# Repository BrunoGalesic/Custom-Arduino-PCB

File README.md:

Custom Arduino UNO-Style Board

This project is a custom-designed Arduino UNO-style board, created with KiCad 8.0, focusing on improved RF characteristics and robust performance. It features a 4-layer PCB design with enhanced power and ground integrity, additional user controls, and thoughtful RF/EMI protections.

 Features:
 
 4-layer PCB with wider power and ground traces for reduced resistance and improved signal integrity.
 
Increased via count on tracks to enhance current capacity and minimize impedance.

Polyfuse for overcurrent protection—resistance increases with temperature rise to protect circuits.

Varistor for surge voltage protection—acts as an insulator under normal conditions and conducts to ground when voltage spikes occur.

Ferrite bead filters (BLM21) to block high-frequency noise while passing low-frequency signals.

USB port shield to mitigate EMI, acting like a Faraday cage connected to ground.

ATmega16U2-MU microcontroller for USB-to-serial conversion, enabling USB communication.

16 MHz external crystal oscillator connected via capacitors for stable clock signals.

4 pushbutton switches and a 7-segment display connected via an I2C port expander for expanded user interaction.

 Design Considerations:
 
 Emphasis on RF performance and signal integrity with multi-layer routing and shielding.
 
Thoughtful placement of components to reduce noise and EMI interference.

Added hardware elements such as TVS diodes for ESD protection on sensitive lines (like RESET).

Designed with educational intent—to explore PCB design, RF characteristics, and protection mechanisms.

 Learning Outcomes:

 The polyfuse: how it increases resistance with temperature due to excessive current.
 
The varistor: how it remains non-conductive at normal voltages and conducts during surges to ground.

The ferrite beads (BLM21): low impedance at low frequencies, high impedance at high frequencies, acting as filters.

USB shielding: how the shield connects to ground and functions like a Faraday cage to prevent EMI.

ATmega16U2-MU: an 8-bit microcontroller used for USB-to-serial conversion.

Crystal oscillators: using piezoelectric effect for stable frequency generation, needing capacitors to ground.

RF oscillators (LC and RC): in radio circuits and microcontrollers.

ICSP (In-Circuit Serial Programming) for direct microcontroller programming.

TXLED and RXLED for visual indication of data transmission and reception.

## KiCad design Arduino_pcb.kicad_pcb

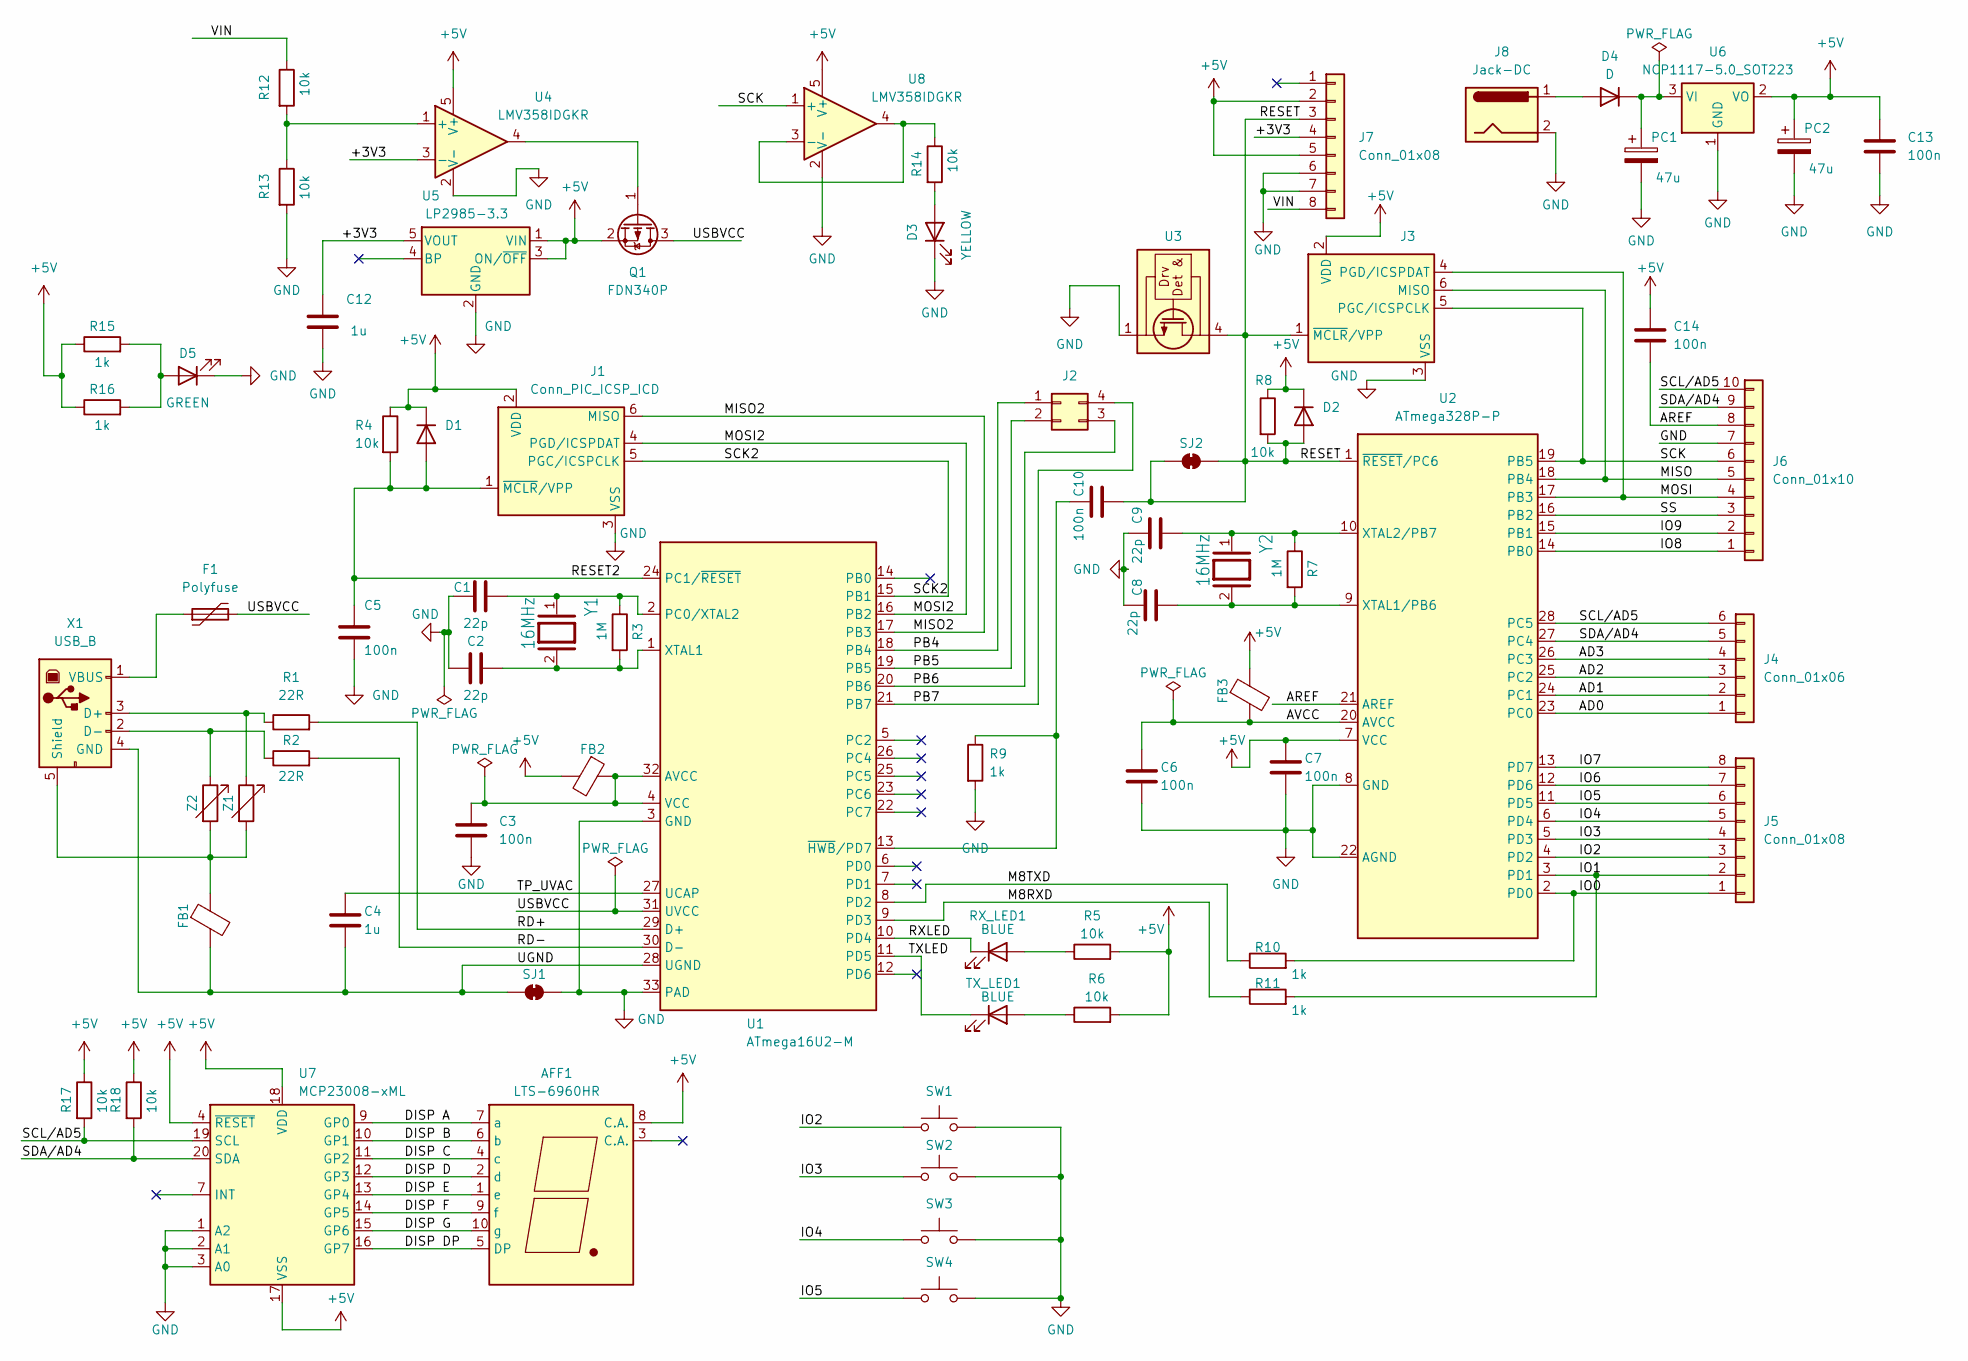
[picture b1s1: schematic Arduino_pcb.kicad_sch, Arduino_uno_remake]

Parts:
AFF1: LTS-6960HR; 7SegmentLED_LTS6760_LTS6780
C1, C2, C8, C9: 22p; C_0402_1005Metric
C3, C5: 100n; C_0603_1608Metric
C4: 1u; C_0603_1608Metric
C6, C7, C10, C13, C14: 100n; C_0201_0603Metric
C12: 1u; C_0201_0603Metric
D1, D2, D4: D; D_0603_1608Metric
D3: YELLOW; LED_0603_1608Metric
D5: GREEN; LED_0603_1608Metric
F1: Polyfuse; Fuse_0603_1608Metric
FB1, FB2, FB3: FerriteBead; L_0805_2012Metric
J1, J3: Conn_PIC_ICSP_ICD; ono
J2: Conn_02x02_Counter_Clockwise; PinHeader_2x02_P2.00mm_Vertical
J4: Conn_01x06; PinHeader_1x06_P1.00mm_Vertical
J5, J7: Conn_01x08; PinHeader_1x08_P1.00mm_Vertical
J6: Conn_01x10; PinHeader_1x10_P1.00mm_Vertical
J8: Jack-DC; BarrelJack_Horizontal
PC1, PC2: 47u; CP_Elec_6.3x5.4
Q1: FDN340P; SOT-23
R1, R2: 22R; R_0603_1608Metric
R3, R7: 1M; R_0603_1608Metric
R4, R5, R6, R8, R12, R13, R14, R17, R18: 10k; R_0603_1608Metric
R9, R10, R11, R15, R16: 1k; R_0603_1608Metric
RX_LED1: BLUE; LED_0603_1608Metric
SJ1, SJ2: SolderJumper_2_Bridged; SolderJumper-2_P1.3mm_Bridged2Bar_Pad1.0x1.5mm
SW1, SW2, SW3, SW4: SW_Push; SW_DIP_SPSTx01_Slide_6.7x4.1mm_W6.73mm_P2.54mm_LowProfile_J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
TX_LED1: BLUE; LED_0603_1608Metric
U1: ATmega16U2-M; QFN-32-1EP_5x5mm_P0.5mm_EP3.1x3.1mm
U2: ATmega328P-P; DIP-28_W7.62mm
U3: TVS3300DRV; WSON-6-1EP_2x2mm_P0.65mm_EP1x1.6mm
U4, U8: LMV358IDGKR; SOP65P490X110-8N
U5: LP2985-3.3; SOT-23-5
U6: NCP1117-5.0_SOT223; SOT-223-3_TabPin2
U7: MCP23008-xML; QFN-20-1EP_4x4mm_P0.5mm_EP2.7x2.7mm
X1: USB_B; USB_B_OST_USB-B1HSxx_Horizontal
Y1, Y2: 16MHz; Crystal_SMD_0603-2Pin_6.0x3.5mm
Z1, Z2: R_Variable; VARC1608X56N

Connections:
+5V: AFF1.8 (C.A.), C7.1, C13.1, C14.1, D1.1 (K), D2.1 (K), FB2.2, FB3.1, J1.2 (VDD), J3.2 (VDD), J7.2, J7.5, PC2.1, Q1.2 (S), R4.1, R5.2, R6.2, R8.1, R15.1, R16.1, R17.1, R18.1, U2.7 (VCC), U4.5 (V+), U5.1 (VIN), U5.3 (ON/~OFF), U6.2 (VO), U7.4 (~RESET), U7.17 (VSS), U7.18 (VDD), U8.5 (V+)
/+3V3: C12.1, J7.4, U4.3 (-), U5.5 (VOUT)
/AD0: J4.1, U2.23 (PC0)
/AD1: J4.2, U2.24 (PC1)
/AD2: J4.3, U2.25 (PC2)
/AD3: J4.4, U2.26 (PC3)
/AREF: C14.2, J6.8, U2.21 (AREF)
/AVCC: C6.1, FB3.2, U2.20 (AVCC)
/DISP A: AFF1.7 (a), U7.9 (GP0)
/DISP B: AFF1.6 (b), U7.10 (GP1)
/DISP C: AFF1.4 (c), U7.11 (GP2)
/DISP D: AFF1.2 (d), U7.12 (GP3)
/DISP DP: AFF1.5 (DP), U7.16 (GP7)
/DISP E: AFF1.1 (e), U7.13 (GP4)
/DISP F: AFF1.9 (f), U7.14 (GP5)
/DISP G: AFF1.10 (g), U7.15 (GP6)
/IO0: J5.1, R10.2, U2.2 (PD0)
/IO1: J5.2, R11.2, U2.3 (PD1)
/IO2: J5.3, SW1.1, U2.4 (PD2)
/IO3: J5.4, SW2.1, U2.5 (PD3)
/IO4: J5.5, SW3.1, U2.6 (PD4)
/IO5: J5.6, SW4.1, U2.11 (PD5)
/IO6: J5.7, U2.12 (PD6)
/IO7: J5.8, U2.13 (PD7)
/IO8: J6.1, U2.14 (PB0)
/IO9: J6.2, U2.15 (PB1)
/M8RXD: R11.1, U1.9 (PD3)
/M8TXD: R10.1, U1.8 (PD2)
/MISO: J3.6 (MISO), J6.5, U2.18 (PB4)
/MISO2: J1.6 (MISO), U1.17 (PB3)
/MOSI: J3.4 (PGD/ICSPDAT), J6.4, U2.17 (PB3)
/MOSI2: J1.4 (PGD/ICSPDAT), U1.16 (PB2)
/PB4: J2.1, U1.18 (PB4)
/PB5: J2.2, U1.19 (PB5)
/PB6: J2.3, U1.20 (PB6)
/PB7: J2.4, U1.21 (PB7)
/RD+: R1.2, U1.29 (D+)
/RD-: R2.2, U1.30 (D-)
/RESET: C10.2, D2.2 (A), J3.1 (~MCLR/VPP), J7.3, R8.2, SJ2.1 (A), SJ2.2 (B), U2.1 (~RESET/PC6), U3.4 (IN), U3.5 (IN), U3.6 (IN)
/RESET2: C5.1, D1.2 (A), J1.1 (~MCLR/VPP), R4.2, U1.24 (PC1/~RESET)
/RXLED: RX_LED1.1 (K), U1.10 (PD4)
/SCK: J3.5 (PGC/ICSPCLK), J6.6, U2.19 (PB5), U8.1 (+)
/SCK2: J1.5 (PGC/ICSPCLK), U1.15 (PB1)
/SCL/AD5: J4.6, J6.10, R17.2, U2.28 (PC5), U7.19 (SCL)
/SDA/AD4: J4.5, J6.9, R18.2, U2.27 (PC4), U7.20 (SDA)
/SS: J6.3, U2.16 (PB2)
/TP_UVAC: C4.1, U1.27 (UCAP)
/TXLED: TX_LED1.1 (K), U1.11 (PD5)
/UGND: C4.2, FB1.2, SJ1.1 (A), U1.28 (UGND), X1.4 (GND)
/USBVCC: F1.2, Q1.3 (D), U1.31 (UVCC)
/VIN: J7.8, R12.1
GND: C1.1, C2.1, C3.2, C5.2, C6.2, C7.2, C8.1, C9.1, C12.2, C13.2, D3.1 (K), D5.1 (K), J1.3 (VSS), J3.3 (VSS), J6.7, J7.6, J7.7, J8.2, PC1.2, PC2.2, R9.2, R13.2, SJ1.2 (B), SW1.2, SW2.2, SW3.2, SW4.2, U1.3 (GND), U1.33 (PAD), U2.8 (GND), U2.22 (AGND), U3.1 (GND), U3.2 (GND), U3.3 (GND), U3.7 (GND), U4.2 (V-), U5.2 (GND), U6.1 (GND), U7.1 (A2), U7.2 (A1), U7.3 (A0), U8.2 (V-)
unnamed: D3.2 (A), R14.2
unnamed: D4.2 (A), J8.1
unnamed: D4.1 (K), PC1.1, U6.3 (VI)
unnamed: D5.2 (A), R15.2, R16.2
unnamed: Q1.1 (G), U4.4
unnamed: R5.1, RX_LED1.2 (A)
unnamed: R6.1, TX_LED1.2 (A)
unnamed: C3.1, FB2.1, U1.4 (VCC), U1.32 (AVCC)
unnamed: C1.2, R3.1, U1.2 (PC0/XTAL2), Y1.1
unnamed: C2.2, R3.2, U1.1 (XTAL1), Y1.2
unnamed: C10.1, R9.1, U1.13 (~HWB/PD7)
unnamed: C8.2, R7.2, U2.9 (XTAL1/PB6), Y2.2
unnamed: C9.2, R7.1, U2.10 (XTAL2/PB7), Y2.1
unnamed: R12.2, R13.1, U4.1 (+)
unnamed: R14.1, U8.3 (-), U8.4
unnamed: R1.1, X1.3 (D+), Z1.1
unnamed: R2.1, X1.2 (D-), Z2.1
unnamed: FB1.1, X1.5 (Shield), Z1.2, Z2.2
unnamed: F1.1, X1.1 (VBUS)

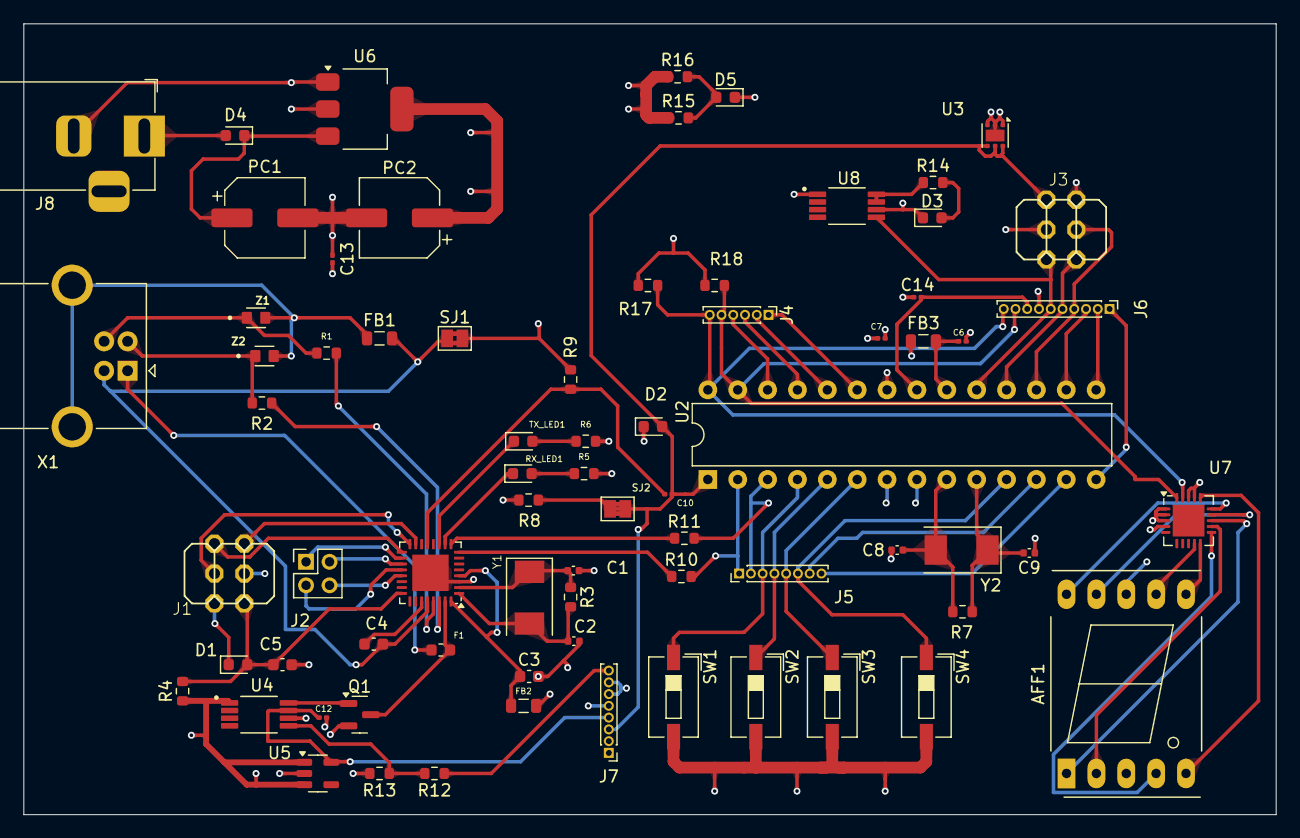
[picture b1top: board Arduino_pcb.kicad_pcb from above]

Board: 4 copper layers, 106.5 x 67.2 mm, 73 parts (0 on the bottom side), 71 nets.

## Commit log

2025-05-31 Create Gerber_files
